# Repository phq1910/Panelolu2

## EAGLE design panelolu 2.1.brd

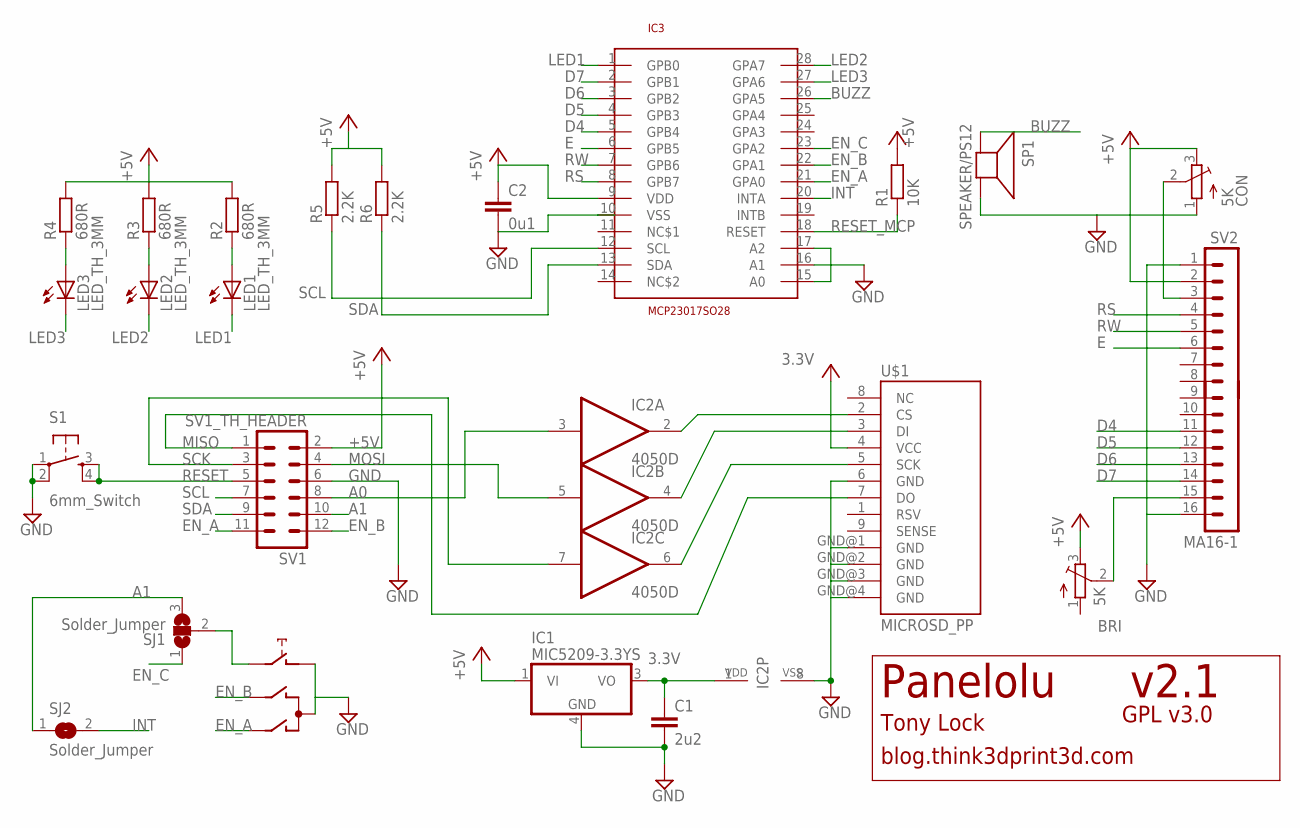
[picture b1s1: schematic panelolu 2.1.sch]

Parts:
BRI: 5K; TC33X
C1: 2u2; C1206K
C2: 0u1; C0805K
CON: 5K; TC33X
IC1: MIC5209-3.3YS; SOT223
IC2: 4050D; SO16
IC3: MCP23017SO28; SO28W
LED1, LED2, LED3: LED_TH_3MM; LED3MM
R1: 10K; M0805
R2, R3, R4: 680R; M0805
R5, R6: 2.2K; M0805
S1: 6mm_Switch; TACTILE-PTH
SJ1: Solder_Jumper; SJ_2
SJ2: Solder_Jumper; SJ
SP1: SPEAKER/PS12; PS12
SV1: SV1_TH_HEADER; MA06-2
SV2: MA16-1
SW1: EC12E_SW; ALPS_EC12E_SW
U$1: MICROSD_PP

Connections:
3.3V: C1.1, IC1.3 (VO), IC2.1 (VDD), U$1.4 (VCC)
+5V: BRI.3 (E), C2.1, CON.3 (E), IC1.1 (VI), IC3.9 (VDD), R1.2, R2.2, R3.2, R4.2, R5.2, R6.2, SV1.2, SV2.2
A0: IC2.3 (I), SV1.8
A1: SJ1.3, SJ2.1, SV1.10
BUZZ: IC3.26 (GPA5), SP1.P$1 (+)
CS3.3: IC2.2 (O), U$1.2 (CS)
D4: IC3.5 (GPB4), SV2.11
D5: IC3.4 (GPB3), SV2.12
D6: IC3.3 (GPB2), SV2.13
D7: IC3.2 (GPB1), SV2.14
DI3.3: IC2.4 (O), U$1.3 (DI)
E: IC3.6 (GPB5), SV2.6
EN_A: IC3.21 (GPA0), SV1.11, SW1.A
EN_B: IC3.22 (GPA1), SV1.12, SW1.B
EN_C: IC3.23 (GPA2), SJ1.1
GND: C1.2, C2.2, CON.1 (A), IC1.4 (GND), IC2.8 (VSS), IC3.10 (VSS), IC3.15 (A0), IC3.16 (A1), IC3.17 (A2), S1.1, S1.2, SP1.P$2 (-), SV1.6, SV2.1, SV2.16, SW1.C, SW1.D (1), U$1.6 (GND), U$1.GND@1 (GND), U$1.GND@2 (GND), U$1.GND@3 (GND), U$1.GND@4 (GND)
INT: IC3.20 (INTA), SJ2.2
LED1: IC3.1 (GPB0), LED1.K (C)
LED2: IC3.28 (GPA7), LED2.K (C)
LED3: IC3.27 (GPA6), LED3.K (C)
MISO: SV1.1, U$1.7 (DO)
MOSI: IC2.5 (I), SV1.4
unnamed: BRI.2 (S), SV2.15
unnamed: CON.2 (S), SV2.3
unnamed: LED1.A, R2.1
unnamed: LED2.A, R3.1
unnamed: LED3.A, R4.1
unnamed: SJ1.2, SW1.E (2)
RESET: S1.3, S1.4, SV1.5
RESET_MCP: IC3.18 (RESET), R1.1
RS: IC3.8 (GPB7), SV2.4
RW: IC3.7 (GPB6), SV2.5
SCK: IC2.7 (I), SV1.3
SCK3.3: IC2.6 (O), U$1.5 (SCK)
SCL: IC3.12 (SCL), R5.1, SV1.7
SDA: IC3.13 (SDA), R6.1, SV1.9

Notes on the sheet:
v2.1
blog.think3dprint3d.com
Tony Lock
GPL v3.0
Panelolu

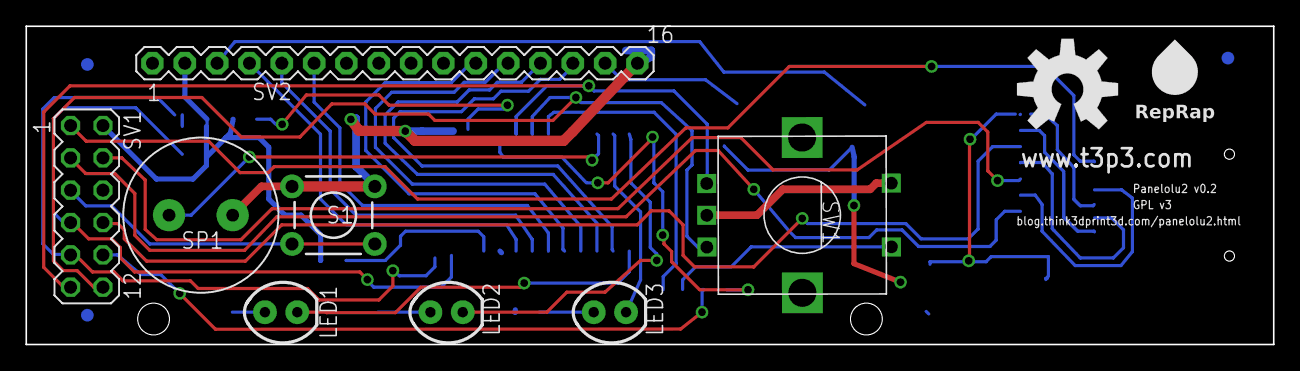
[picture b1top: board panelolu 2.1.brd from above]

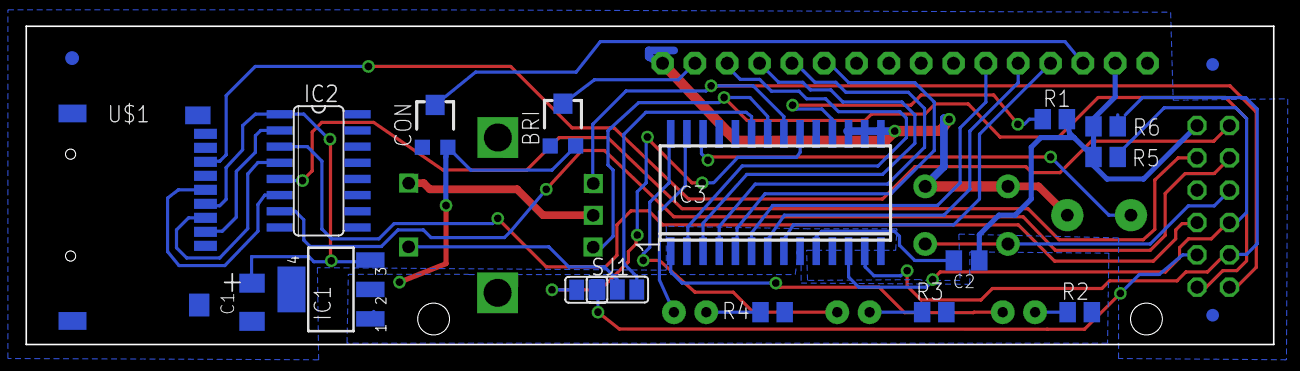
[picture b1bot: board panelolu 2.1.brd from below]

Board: 2 copper layers, 98.0 x 25.0 mm, 24 parts (16 on the bottom side), 36 nets.

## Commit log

2013-07-05 Create BOM_Exp_Board_Slolu.txt
    Bom file Exp for Sanguinololu
2013-07-05 Create BOM_panelolu2.1.txt
    Bom file panelolu 2.1
2013-07-05 Update panelolu 2.1.brd
    Change voltage regulator MIC5209-3.3YS
2013-07-05 Update panelolu 2.1.sch
    change regulator voltage
2013-07-05 Update Exp_Board_Slolu.sch
    include transistor Q1 and Q2 value
